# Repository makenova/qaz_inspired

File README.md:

# qaz_inspired

My take on a qaz inspired boards. Mostly the difference is integrated mcu.

## qaz_m **untested**

- integrated mcu
- shifted bottom row

## qazv4n_m **untested**

- integrated mcu
- hotswap
- shifted bottom row
- removable gamer row

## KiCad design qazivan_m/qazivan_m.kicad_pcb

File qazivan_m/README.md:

# qaziv4n

My take on an integrated mcu hot-swap [qaz](https://www.cbkbd.com/product/qaz-keyboard-kit) with a [van](https://trashman.wiki/en/keyboards/v4n4g0n) backspace and gamer row.

The plate file can be found in the [docs](./docs) folder.

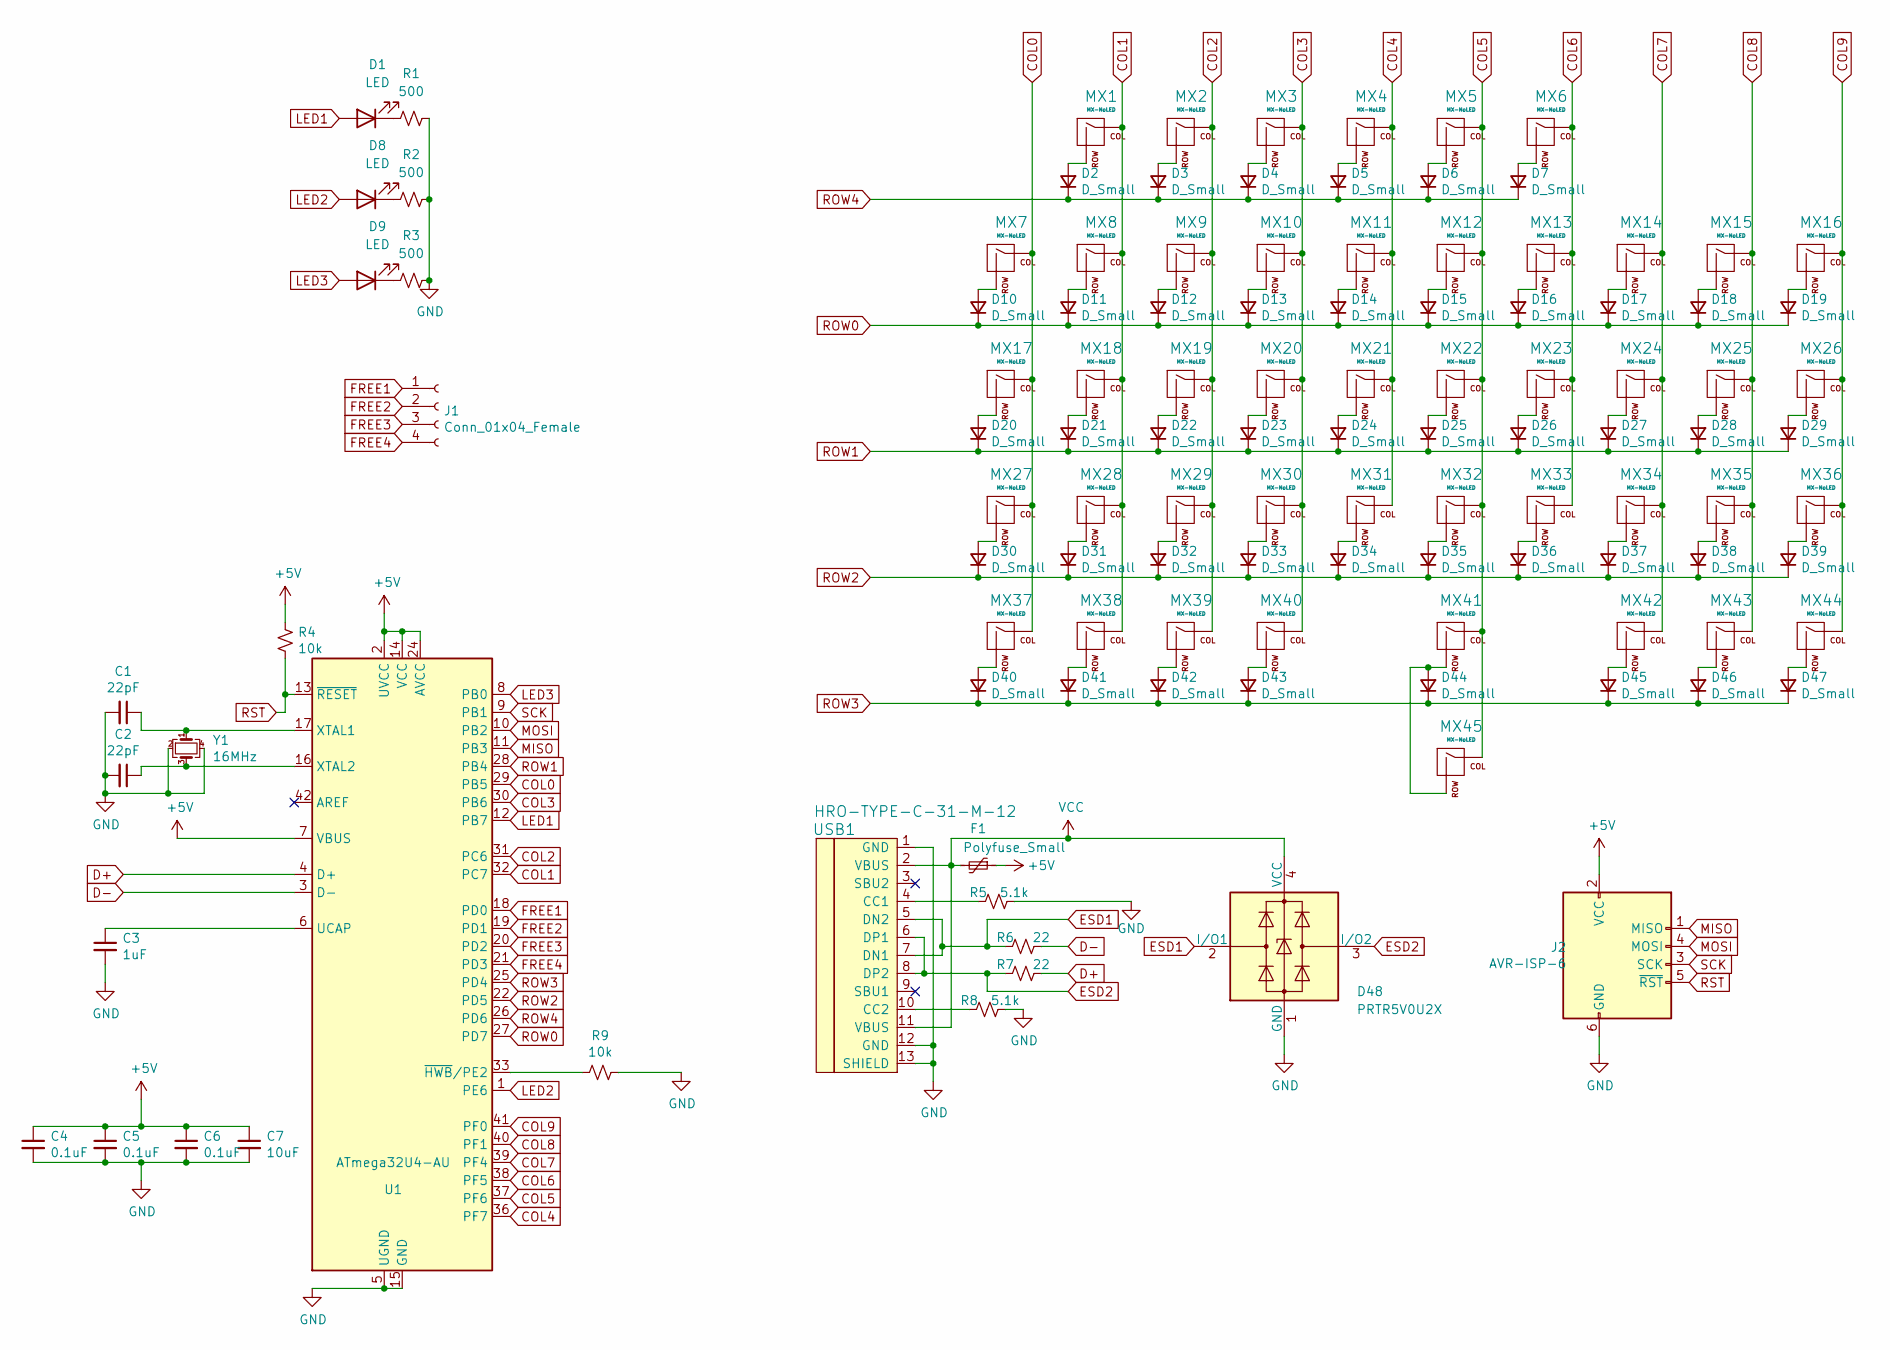
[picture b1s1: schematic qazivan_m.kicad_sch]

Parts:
C1, C2: 22pF; C_0805_2012Metric; LCSC C1804
C3: 1uF; C_0805_2012Metric; LCSC C28323
C4, C5, C6: 0.1uF; C_0805_2012Metric; LCSC C49678
C7: 10uF; C_0805_2012Metric; LCSC C307523
D1, D8, D9: LED; LED_0805_2012Metric
D2, D3, D4, D5, D6, D7, D10, D11, D12, D13, D14, D15, D16, D17, D18, D19, D20, D21, D22, D23, D24, D25, D26, D27, D28, D29, D30, D31, D32, D33, D34, D35, D36, D37, D38, D39, D40, D41, D42, D43, D44, D45, D46, D47: D_Small; D_SOD-123; LCSC C81598
D48: PRTR5V0U2X; SOT143B; LCSC C78442
F1: Polyfuse_Small; Fuse_1206_3216Metric; LCSC C151162
J1: Conn_01x04_Female; JST_ZE_B04B-ZESK-D_1x04_P1.50mm_Vertical
J2: AVR-ISP-6; Reset_Pretty
MX1, MX2, MX3, MX4, MX5, MX6, MX7, MX8, MX9, MX10, MX11, MX12, MX13, MX14, MX15, MX18, MX19, MX20, MX21, MX22, MX23, MX24, MX25, MX28, MX29, MX30, MX31, MX32, MX33, MX34, MX35, MX36, MX38, MX39, MX42, MX43: MX-NoLED; MXOnly-1U-Hotswap
MX16, MX27: MX-NoLED; MXOnly-1.75U-Hotswap
MX17, MX37, MX44: MX-NoLED; MXOnly-1.25U-Hotswap
MX26: MX-NoLED; MXOnly-1.5U-Hotswap
MX40: MX-NoLED; MXOnly-2.25U-Hotswap-ReversedStabilizers
MX41: MX-NoLED; MXOnly-2U-Hotswap-ReversedStabilizers
MX45: MX-NoLED; MXOnly-6.25U-Hotswap-ReversedStabilizers
R1, R2, R3: 500; R_0805_2012Metric
R4, R9: 10k; R_0805_2012Metric; LCSC C17414
R5, R8: 5.1k; R_0805_2012Metric; LCSC C27834
R6, R7: 22; R_0805_2012Metric; LCSC C17561
U1: ATmega32U4-AU; TQFP-44_10x10mm_P0.8mm; LCSC C44854
USB1: HRO-TYPE-C-31-M-12; HRO-TYPE-C-31-M-12-HandSoldering
Y1: 16MHz; Crystal_SMD_3225-4Pin_3.2x2.5mm; LCSC C89379

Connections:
+5V: C4.1, C5.1, C6.1, C7.1, F1.1, J2.2 (VCC), R4.1, U1.2 (UVCC), U1.7 (VBUS), U1.14 (VCC), U1.24 (AVCC), U1.34 (VCC), U1.44 (AVCC)
COL0: MX7.1 (COL), MX17.1 (COL), MX27.1 (COL), MX37.1 (COL), U1.29 (PB5)
COL1: MX1.1 (COL), MX8.1 (COL), MX18.1 (COL), MX28.1 (COL), MX38.1 (COL), U1.32 (PC7)
COL2: MX2.1 (COL), MX9.1 (COL), MX19.1 (COL), MX29.1 (COL), MX39.1 (COL), U1.31 (PC6)
COL3: MX3.1 (COL), MX10.1 (COL), MX20.1 (COL), MX30.1 (COL), MX40.1 (COL), U1.30 (PB6)
COL4: MX4.1 (COL), MX11.1 (COL), MX21.1 (COL), MX31.1 (COL), U1.36 (PF7)
COL5: MX5.1 (COL), MX12.1 (COL), MX22.1 (COL), MX32.1 (COL), MX41.1 (COL), MX45.1 (COL), U1.37 (PF6)
COL6: MX6.1 (COL), MX13.1 (COL), MX23.1 (COL), MX33.1 (COL), U1.38 (PF5)
COL7: MX14.1 (COL), MX24.1 (COL), MX34.1 (COL), MX42.1 (COL), U1.39 (PF4)
COL8: MX15.1 (COL), MX25.1 (COL), MX35.1 (COL), MX43.1 (COL), U1.40 (PF1)
COL9: MX16.1 (COL), MX26.1 (COL), MX36.1 (COL), MX44.1 (COL), U1.41 (PF0)
D+: R7.1, U1.4 (D+)
D-: R6.1, U1.3 (D-)
ESD1: D48.2 (I/O1), R6.2, USB1.5 (DN2), USB1.7 (DN1)
ESD2: D48.3 (I/O2), R7.2, USB1.6 (DP1), USB1.8 (DP2)
FREE1: J1.1, U1.18 (PD0)
FREE2: J1.2, U1.19 (PD1)
FREE3: J1.3, U1.20 (PD2)
FREE4: J1.4, U1.21 (PD3)
GND: C1.2, C2.2, C3.2, C4.2, C5.2, C6.2, C7.2, D48.1 (GND), J2.6 (GND), R1.2, R2.2, R3.2, R5.1, R8.1, R9.1, U1.5 (UGND), U1.15 (GND), U1.23 (GND), U1.35 (GND), U1.43 (GND), USB1.1 (GND), USB1.12 (GND), USB1.13 (SHIELD), Y1.2, Y1.4
LED1: D1.2 (A), U1.12 (PB7)
LED2: D8.2 (A), U1.1 (PE6)
LED3: D9.2 (A), U1.8 (PB0)
MISO: J2.1 (MISO), U1.11 (PB3)
MOSI: J2.4 (MOSI), U1.10 (PB2)
unnamed: C1.1, U1.17 (XTAL1), Y1.1
unnamed: C2.1, U1.16 (XTAL2), Y1.3
unnamed: C3.1, U1.6 (UCAP)
unnamed: D1.1 (K), R1.1
unnamed: D2.2 (A), MX1.2 (ROW)
unnamed: D3.2 (A), MX2.2 (ROW)
unnamed: D4.2 (A), MX3.2 (ROW)
unnamed: D5.2 (A), MX4.2 (ROW)
unnamed: D6.2 (A), MX5.2 (ROW)
unnamed: D7.2 (A), MX6.2 (ROW)
unnamed: D8.1 (K), R2.1
unnamed: D9.1 (K), R3.1
unnamed: D10.2 (A), MX7.2 (ROW)
unnamed: D11.2 (A), MX8.2 (ROW)
unnamed: D12.2 (A), MX9.2 (ROW)
unnamed: D13.2 (A), MX10.2 (ROW)
unnamed: D14.2 (A), MX11.2 (ROW)
unnamed: D15.2 (A), MX12.2 (ROW)
unnamed: D16.2 (A), MX13.2 (ROW)
unnamed: D17.2 (A), MX14.2 (ROW)
unnamed: D18.2 (A), MX15.2 (ROW)
unnamed: D19.2 (A), MX16.2 (ROW)
unnamed: D20.2 (A), MX17.2 (ROW)
unnamed: D21.2 (A), MX18.2 (ROW)
unnamed: D22.2 (A), MX19.2 (ROW)
unnamed: D23.2 (A), MX20.2 (ROW)
unnamed: D24.2 (A), MX21.2 (ROW)
unnamed: D25.2 (A), MX22.2 (ROW)
unnamed: D26.2 (A), MX23.2 (ROW)
unnamed: D27.2 (A), MX24.2 (ROW)
unnamed: D28.2 (A), MX25.2 (ROW)
unnamed: D29.2 (A), MX26.2 (ROW)
unnamed: D30.2 (A), MX27.2 (ROW)
unnamed: D31.2 (A), MX28.2 (ROW)
unnamed: D32.2 (A), MX29.2 (ROW)
unnamed: D33.2 (A), MX30.2 (ROW)
unnamed: D34.2 (A), MX31.2 (ROW)
unnamed: D35.2 (A), MX32.2 (ROW)
unnamed: D36.2 (A), MX33.2 (ROW)
unnamed: D37.2 (A), MX34.2 (ROW)
unnamed: D38.2 (A), MX35.2 (ROW)
unnamed: D39.2 (A), MX36.2 (ROW)
unnamed: D40.2 (A), MX37.2 (ROW)
unnamed: D41.2 (A), MX38.2 (ROW)
unnamed: D42.2 (A), MX39.2 (ROW)
unnamed: D43.2 (A), MX40.2 (ROW)
unnamed: D44.2 (A), MX41.2 (ROW), MX45.2 (ROW)
unnamed: D45.2 (A), MX42.2 (ROW)
unnamed: D46.2 (A), MX43.2 (ROW)
unnamed: D47.2 (A), MX44.2 (ROW)
unnamed: R5.2, USB1.4 (CC1)
unnamed: R8.2, USB1.10 (CC2)
unnamed: R9.2, U1.33 (~HWB/PE2)
ROW0: D10.1 (K), D11.1 (K), D12.1 (K), D13.1 (K), D14.1 (K), D15.1 (K), D16.1 (K), D17.1 (K), D18.1 (K), D19.1 (K), U1.27 (PD7)
ROW1: D20.1 (K), D21.1 (K), D22.1 (K), D23.1 (K), D24.1 (K), D25.1 (K), D26.1 (K), D27.1 (K), D28.1 (K), D29.1 (K), U1.28 (PB4)
ROW2: D30.1 (K), D31.1 (K), D32.1 (K), D33.1 (K), D34.1 (K), D35.1 (K), D36.1 (K), D37.1 (K), D38.1 (K), D39.1 (K), U1.22 (PD5)
ROW3: D40.1 (K), D41.1 (K), D42.1 (K), D43.1 (K), D44.1 (K), D45.1 (K), D46.1 (K), D47.1 (K), U1.25 (PD4)
ROW4: D2.1 (K), D3.1 (K), D4.1 (K), D5.1 (K), D6.1 (K), D7.1 (K), U1.26 (PD6)
RST: J2.5 (~RST), R4.2, U1.13 (~RESET)
SCK: J2.3 (SCK), U1.9 (PB1)
VCC: D48.4 (VCC), F1.2, USB1.2 (VBUS), USB1.11 (VBUS)

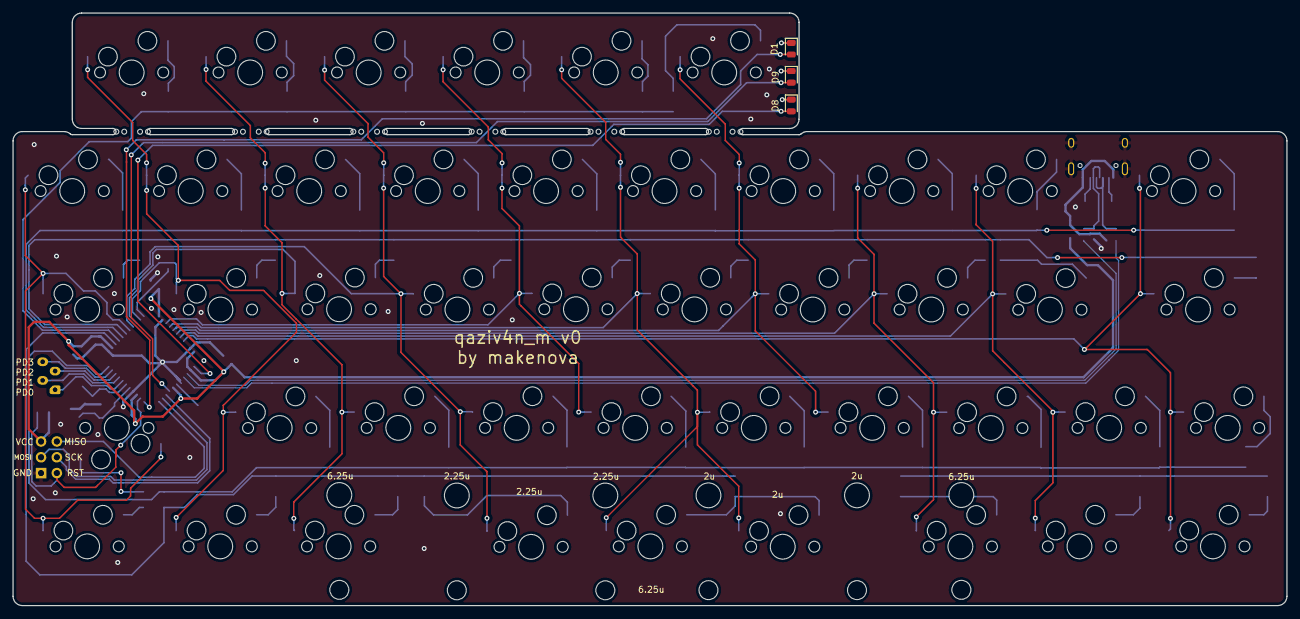
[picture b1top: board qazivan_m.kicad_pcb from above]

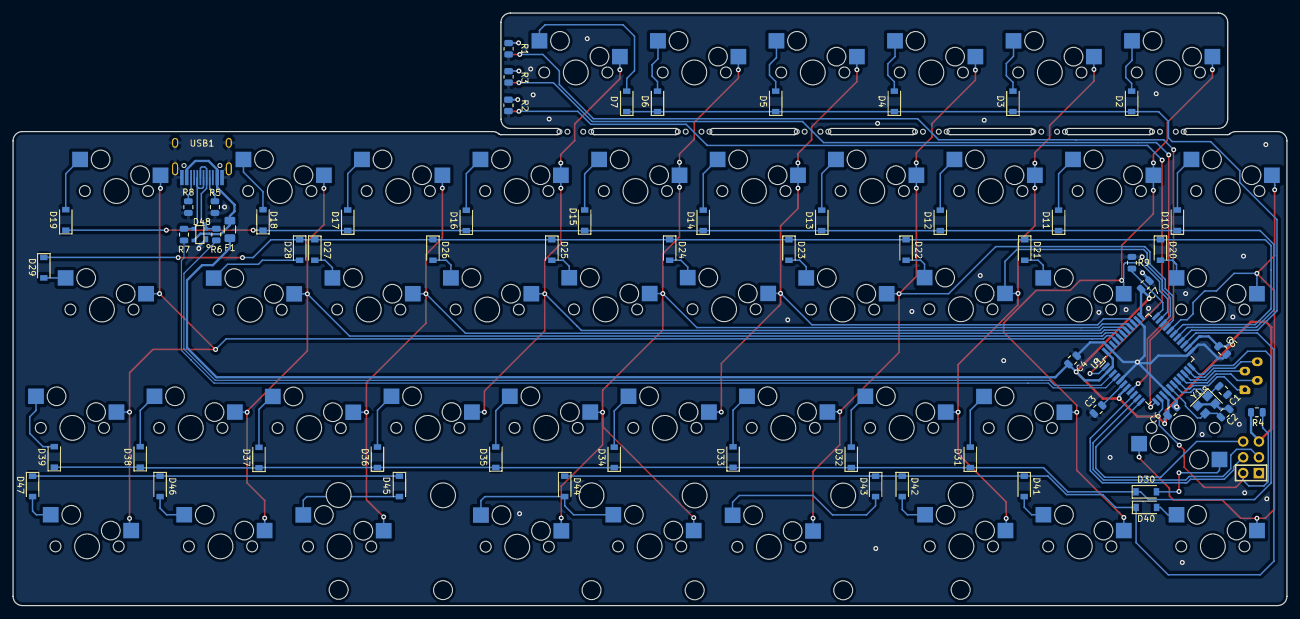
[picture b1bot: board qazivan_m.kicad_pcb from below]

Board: 2 copper layers, 204.8 x 95.2 mm, 115 parts (66 on the bottom side), 86 nets.

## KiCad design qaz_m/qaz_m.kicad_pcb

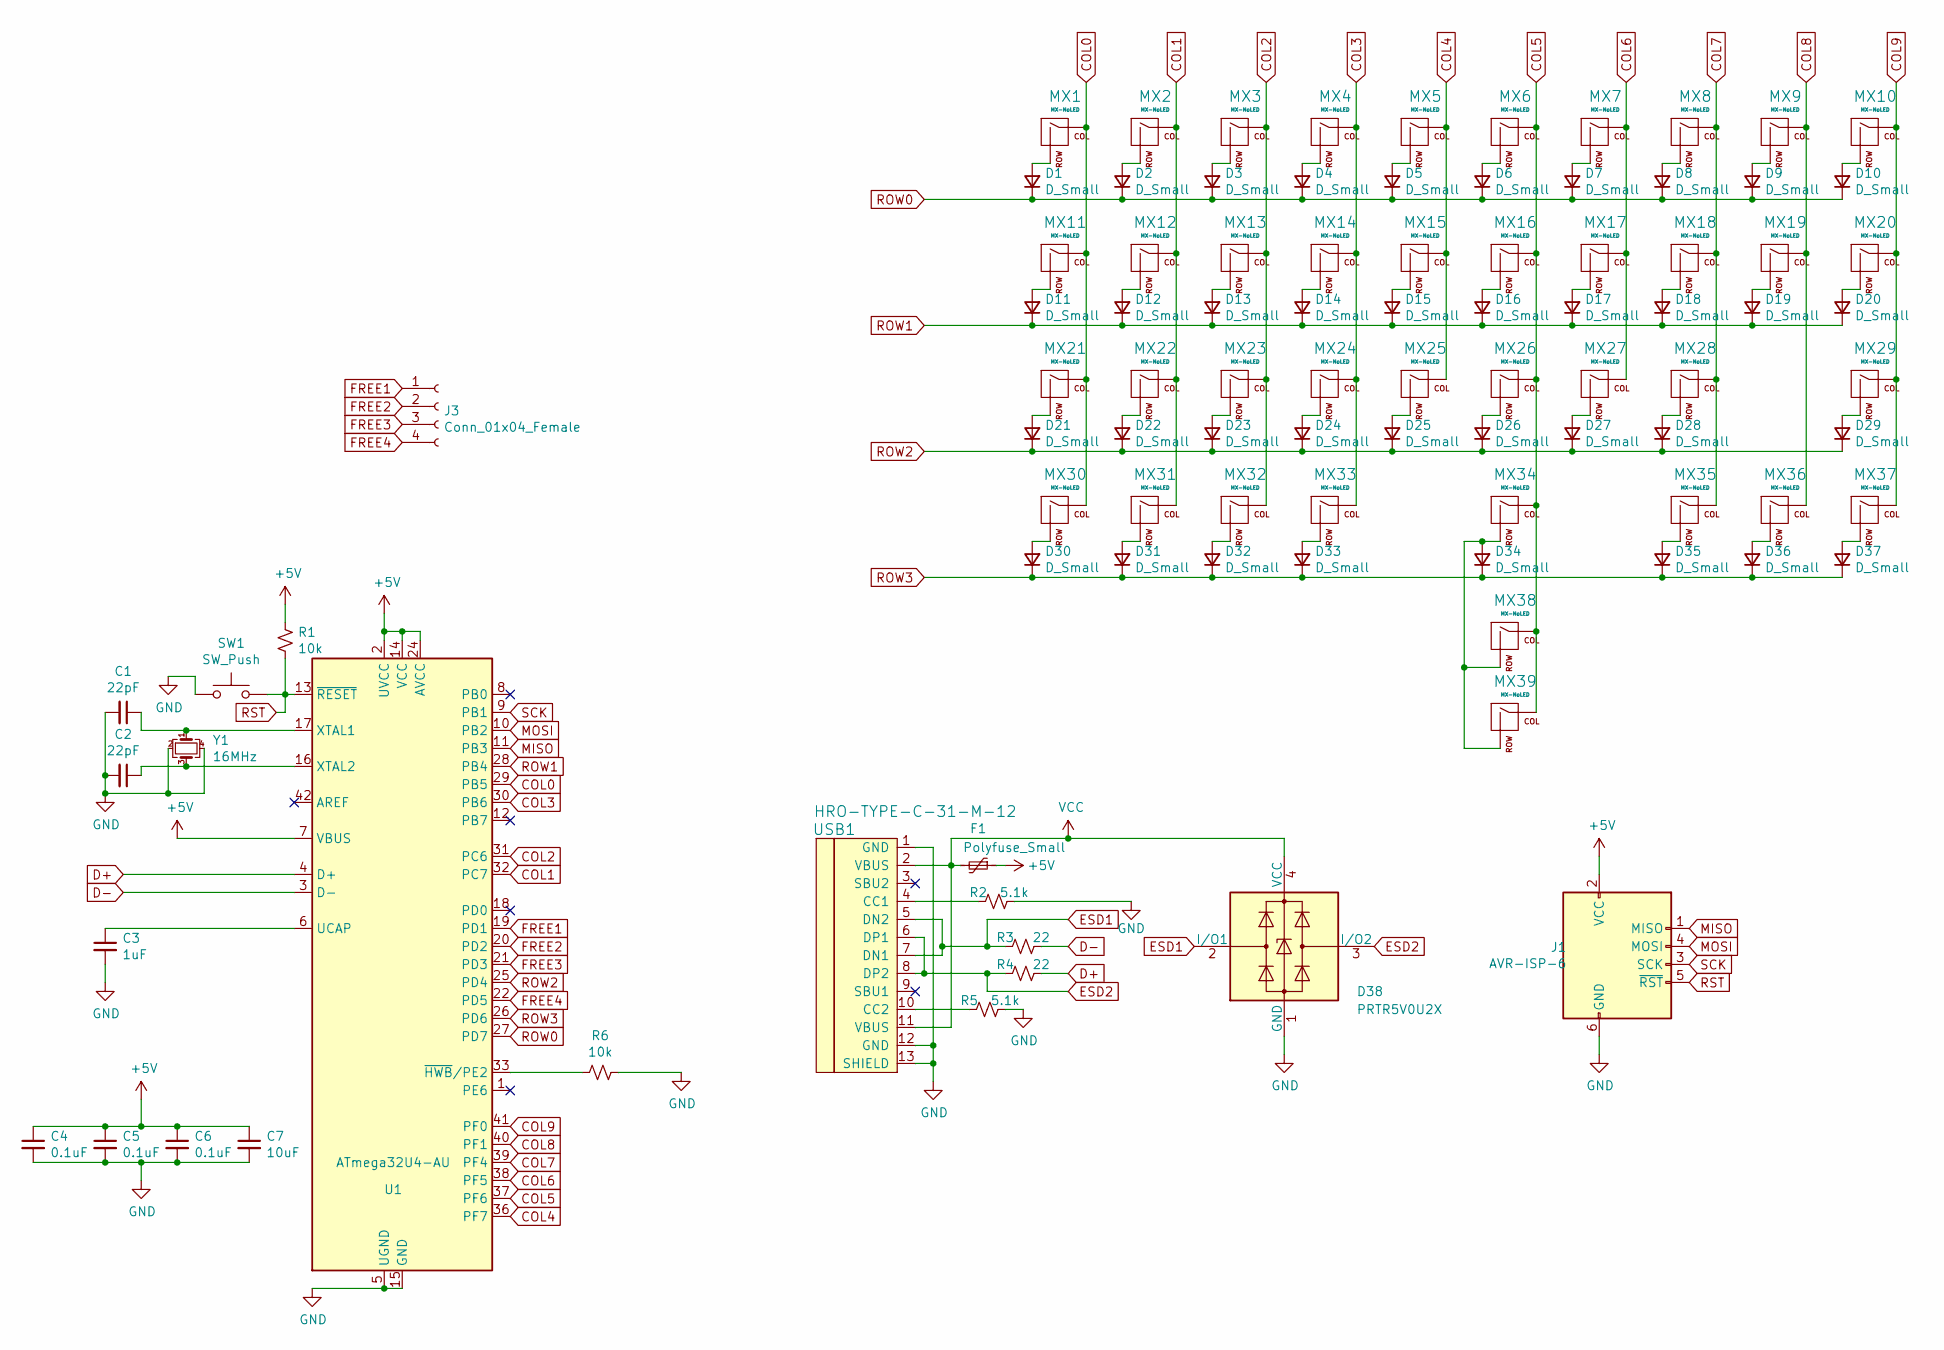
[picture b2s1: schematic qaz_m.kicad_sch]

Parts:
C1, C2: 22pF; C_0805_2012Metric; LCSC C1804
C3: 1uF; C_0805_2012Metric; LCSC C28323
C4, C5, C6: 0.1uF; C_0805_2012Metric; LCSC C49678
C7: 10uF; C_0805_2012Metric; LCSC C307523
D1, D2, D3, D4, D5, D6, D7, D8, D9, D10, D11, D12, D13, D14, D15, D16, D17, D18, D19, D20, D21, D22, D23, D24, D25, D26, D27, D28, D29, D30, D31, D32, D33, D34, D35, D36, D37: D_Small; D_SOD-123; LCSC C81598
D38: PRTR5V0U2X; SOT143B; LCSC C78442
F1: Polyfuse_Small; Fuse_1206_3216Metric; LCSC C151162
J1: AVR-ISP-6; Reset_Pretty
J3: Conn_01x04_Female; JST_ZE_B04B-ZESK-D_1x04_P1.50mm_Vertical
MX1, MX2, MX3, MX4, MX5, MX6, MX7, MX8, MX9, MX12, MX13, MX14, MX15, MX16, MX17, MX18, MX19, MX20, MX22, MX23, MX24, MX25, MX26, MX27, MX28, MX30, MX31, MX32, MX35, MX36, MX37: MX-NoLED; MXOnly-1U-NoLED
MX10, MX11: MX-NoLED; MXOnly-1.25U-NoLED
MX21: MX-NoLED; MXOnly-1.75U-NoLED
MX29: MX-NoLED; MXOnly-1.5U-NoLED
MX33: MX-NoLED; MXOnly-2.25U-ReversedStabilizers-NoLED
MX34: MX-NoLED; MXOnly-2U-ReversedStabilizers-NoLED
MX38, MX39: MX-NoLED; MXOnly-6.25U-ReversedStabilizers-NoLED
R1, R6: 10k; R_0805_2012Metric; LCSC C17414
R2, R5: 5.1k; R_0805_2012Metric; LCSC C27834
R3, R4: 22; R_0805_2012Metric; LCSC C17561
SW1: SW_Push; SKQG-1155865; LCSC C318884
U1: ATmega32U4-AU; TQFP-44_10x10mm_P0.8mm; LCSC C44854
USB1: HRO-TYPE-C-31-M-12; HRO-TYPE-C-31-M-12-HandSoldering
Y1: 16MHz; Crystal_SMD_3225-4Pin_3.2x2.5mm; LCSC C89379

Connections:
+5V: C4.1, C5.1, C6.1, C7.1, F1.1, J1.2 (VCC), R1.1, U1.2 (UVCC), U1.7 (VBUS), U1.14 (VCC), U1.24 (AVCC), U1.34 (VCC), U1.44 (AVCC)
COL0: MX1.1 (COL), MX11.1 (COL), MX21.1 (COL), MX30.1 (COL), U1.29 (PB5)
COL1: MX2.1 (COL), MX12.1 (COL), MX22.1 (COL), MX31.1 (COL), U1.32 (PC7)
COL2: MX3.1 (COL), MX13.1 (COL), MX23.1 (COL), MX32.1 (COL), U1.31 (PC6)
COL3: MX4.1 (COL), MX14.1 (COL), MX24.1 (COL), MX33.1 (COL), U1.30 (PB6)
COL4: MX5.1 (COL), MX15.1 (COL), MX25.1 (COL), U1.36 (PF7)
COL5: MX6.1 (COL), MX16.1 (COL), MX26.1 (COL), MX34.1 (COL), MX38.1 (COL), MX39.1 (COL), U1.37 (PF6)
COL6: MX7.1 (COL), MX17.1 (COL), MX27.1 (COL), U1.38 (PF5)
COL7: MX8.1 (COL), MX18.1 (COL), MX28.1 (COL), MX35.1 (COL), U1.39 (PF4)
COL8: MX9.1 (COL), MX19.1 (COL), MX36.1 (COL), U1.40 (PF1)
COL9: MX10.1 (COL), MX20.1 (COL), MX29.1 (COL), MX37.1 (COL), U1.41 (PF0)
D+: R4.1, U1.4 (D+)
D-: R3.1, U1.3 (D-)
ESD1: D38.2 (I/O1), R3.2, USB1.5 (DN2), USB1.7 (DN1)
ESD2: D38.3 (I/O2), R4.2, USB1.6 (DP1), USB1.8 (DP2)
FREE1: J3.1, U1.19 (PD1)
FREE2: J3.2, U1.20 (PD2)
FREE3: J3.3, U1.21 (PD3)
FREE4: J3.4, U1.22 (PD5)
GND: C1.2, C2.2, C3.2, C4.2, C5.2, C6.2, C7.2, D38.1 (GND), J1.6 (GND), R2.1, R5.1, R6.1, SW1.1, U1.5 (UGND), U1.15 (GND), U1.23 (GND), U1.35 (GND), U1.43 (GND), USB1.1 (GND), USB1.12 (GND), USB1.13 (SHIELD), Y1.2, Y1.4
MISO: J1.1 (MISO), U1.11 (PB3)
MOSI: J1.4 (MOSI), U1.10 (PB2)
unnamed: C1.1, U1.17 (XTAL1), Y1.1
unnamed: C2.1, U1.16 (XTAL2), Y1.3
unnamed: C3.1, U1.6 (UCAP)
unnamed: D1.2 (A), MX1.2 (ROW)
unnamed: D2.2 (A), MX2.2 (ROW)
unnamed: D3.2 (A), MX3.2 (ROW)
unnamed: D4.2 (A), MX4.2 (ROW)
unnamed: D5.2 (A), MX5.2 (ROW)
unnamed: D6.2 (A), MX6.2 (ROW)
unnamed: D7.2 (A), MX7.2 (ROW)
unnamed: D8.2 (A), MX8.2 (ROW)
unnamed: D9.2 (A), MX9.2 (ROW)
unnamed: D10.2 (A), MX10.2 (ROW)
unnamed: D11.2 (A), MX11.2 (ROW)
unnamed: D12.2 (A), MX12.2 (ROW)
unnamed: D13.2 (A), MX13.2 (ROW)
unnamed: D14.2 (A), MX14.2 (ROW)
unnamed: D15.2 (A), MX15.2 (ROW)
unnamed: D16.2 (A), MX16.2 (ROW)
unnamed: D17.2 (A), MX17.2 (ROW)
unnamed: D18.2 (A), MX18.2 (ROW)
unnamed: D19.2 (A), MX19.2 (ROW)
unnamed: D20.2 (A), MX20.2 (ROW)
unnamed: D21.2 (A), MX21.2 (ROW)
unnamed: D22.2 (A), MX22.2 (ROW)
unnamed: D23.2 (A), MX23.2 (ROW)
unnamed: D24.2 (A), MX24.2 (ROW)
unnamed: D25.2 (A), MX25.2 (ROW)
unnamed: D26.2 (A), MX26.2 (ROW)
unnamed: D27.2 (A), MX27.2 (ROW)
unnamed: D28.2 (A), MX28.2 (ROW)
unnamed: D29.2 (A), MX29.2 (ROW)
unnamed: D30.2 (A), MX30.2 (ROW)
unnamed: D31.2 (A), MX31.2 (ROW)
unnamed: D32.2 (A), MX32.2 (ROW)
unnamed: D33.2 (A), MX33.2 (ROW)
unnamed: D34.2 (A), MX34.2 (ROW), MX38.2 (ROW), MX39.2 (ROW)
unnamed: D35.2 (A), MX35.2 (ROW)
unnamed: D36.2 (A), MX36.2 (ROW)
unnamed: D37.2 (A), MX37.2 (ROW)
unnamed: R2.2, USB1.4 (CC1)
unnamed: R5.2, USB1.10 (CC2)
unnamed: R6.2, U1.33 (~HWB/PE2)
ROW0: D1.1 (K), D2.1 (K), D3.1 (K), D4.1 (K), D5.1 (K), D6.1 (K), D7.1 (K), D8.1 (K), D9.1 (K), D10.1 (K), U1.27 (PD7)
ROW1: D11.1 (K), D12.1 (K), D13.1 (K), D14.1 (K), D15.1 (K), D16.1 (K), D17.1 (K), D18.1 (K), D19.1 (K), D20.1 (K), U1.28 (PB4)
ROW2: D21.1 (K), D22.1 (K), D23.1 (K), D24.1 (K), D25.1 (K), D26.1 (K), D27.1 (K), D28.1 (K), D29.1 (K), U1.25 (PD4)
ROW3: D30.1 (K), D31.1 (K), D32.1 (K), D33.1 (K), D34.1 (K), D35.1 (K), D36.1 (K), D37.1 (K), U1.26 (PD6)
RST: J1.5 (~RST), R1.2, SW1.2, U1.13 (~RESET)
SCK: J1.3 (SCK), U1.9 (PB1)
VCC: D38.4 (VCC), F1.2, USB1.2 (VBUS), USB1.11 (VBUS)

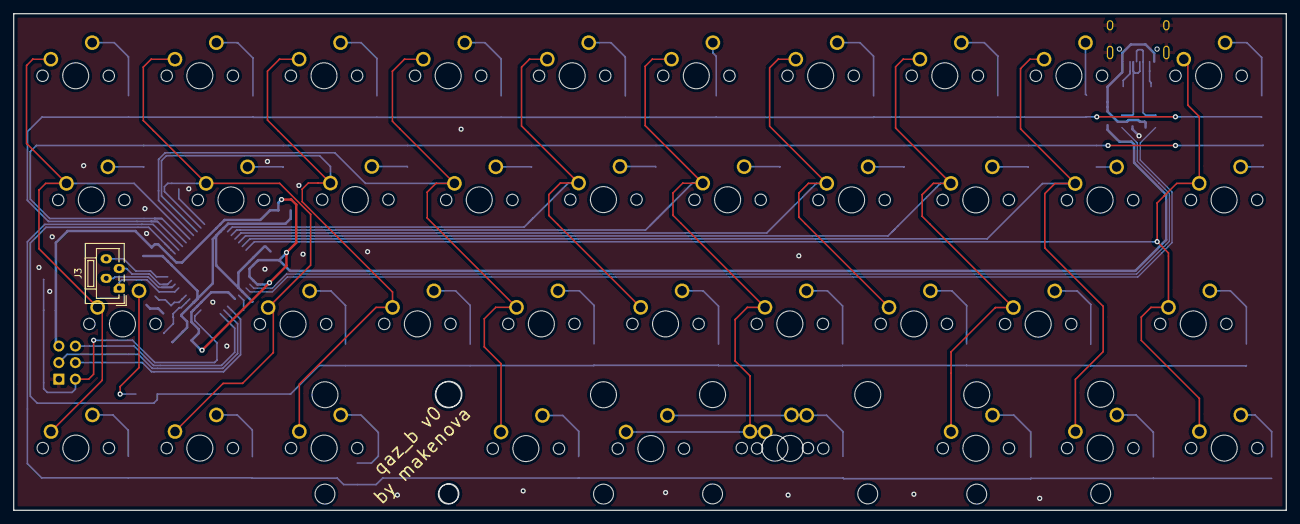
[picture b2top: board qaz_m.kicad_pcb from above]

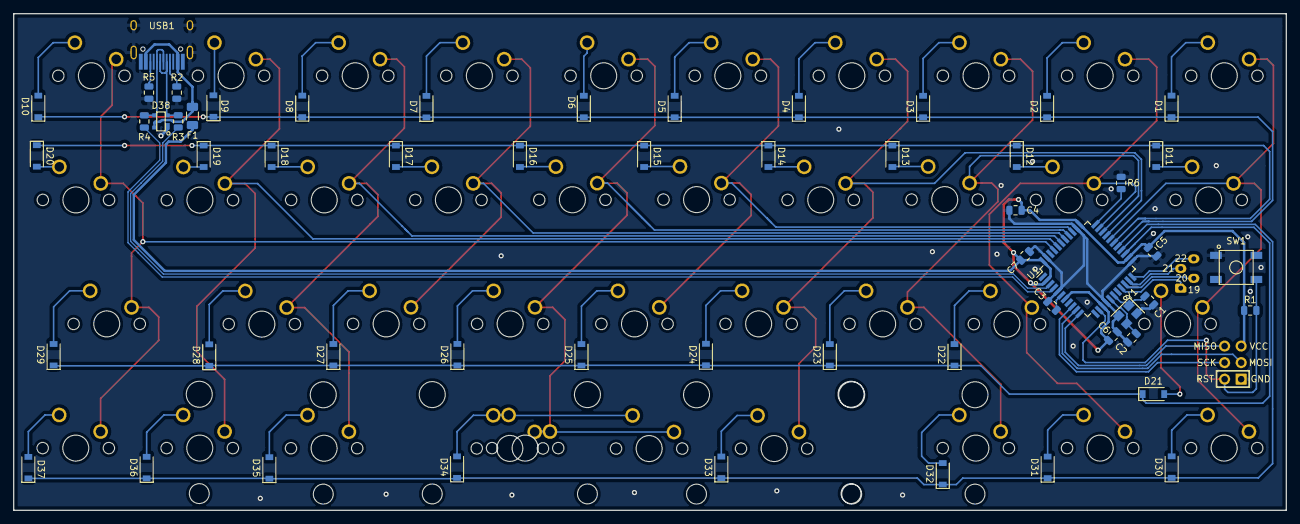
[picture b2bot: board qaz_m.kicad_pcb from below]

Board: 2 copper layers, 195.3 x 76.2 mm, 97 parts (57 on the bottom side), 72 nets.

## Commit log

2020-09-21 make it so
    note: consider repositioning unused pins breakout so that it is not below a switch.
2022-03-03 initial draft of qazivan_m
    the bottom rows do not work because of some overlap.
2022-03-03 fixed bottom row, adding gamer row
2022-03-04 add indicator leds. need to figure out mouting
2022-03-06 fix indicator leds
    mcu pin to anode not cathode
2022-03-06 update bottom row
2022-03-06 generate gerbers
2022-04-19 center big bar
